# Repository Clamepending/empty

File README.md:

# PCB-Repair

PCB-Repair is a reinforcement-learning environment and evaluation in which an agent repairs small
printed-circuit-board designs. Each design has a schematic of record (`design.json`) and a KiCad 7
layout (`board.kicad_pcb`). Each normal-tier task contains 1–3 injected faults: wrong component
values, broken or swapped connections, wrong footprints, undersized power tracks, misplaced
decoupling capacitors, and so on. Hard-tier tasks (mostly 20–27-part multi-rail boards) contain
3–6 faults, at least two of them *latent*: invisible to every `pcbtool` check but deducible from the
datasheets, the design intent and the stated design rules. The agent works with ordinary shell commands plus a domain CLI (`pcbtool`). A
deterministic verifier then grades the two deliverable files against a hidden golden reference.
The verifier applies structural gates and also runs KiCad DRC, an ERC, SPICE spec assertions
(ngspice) and layout checks. The reward is binary: it is 1 only if every gate and check passes.
Because the reward is checked rather than judged by a model, it equals correctness. Every task is
procedurally generated, so the generator can produce fresh, uncontaminated tasks on demand.

## Quickstart (Ubuntu 24.04, about 10 min)

Run every command from the repo root, in order. Each one was timed on a 4-core host (see
`docs/ONBOARDING.md` for the measured times). Nothing here needs network access or Docker.

### 0. Preflight

```bash
python3 -c "import pcbnew, numpy, yaml; print('ok', pcbnew.Version())" && ngspice --version | grep -m1 ngspice
```

This must print `ok 7.0.11` and an `ngspice-42` line. If it does not:

- **KiCad 7.0.11 and ngspice** come from apt: `sudo apt-get install -y kicad=7.0.11* kicad-footprints=7.0.11* ngspice`.
  The `pcbnew` module lands in `/usr/lib/python3/dist-packages`. It works with whichever `python3` the
  apt KiCad build supports. On the reference host that is Python 3.13. `pcbnew` is not on PyPI.
- **numpy, pyyaml and pytest** come from pip for that same `python3`:
  `python3 -m pip install numpy pyyaml pytest`.
  On a stock Ubuntu 24.04 python (3.12, "externally managed") you need either `--break-system-packages`
  or the apt packages `python3-numpy python3-yaml python3-pytest`.
  The apt packages are built for the distro python only. If your `python3` is a different version
  (as on the reference host, 3.13), they are invisible to it and you must use pip.
- Alternatively, use a venv that can see `pcbnew`:
  `python3 -m venv --system-site-packages .venv && . .venv/bin/activate && pip install -e .`
  This was tested: it also puts `pcbtool` on PATH and makes `import pcbenv` work from any directory.

### 1. Get tasks

The bundles in `dist/` are extracted into `data/v2/<split>/<task_id>/`. That is the same layout as
`tasks/v2/` in a git checkout, so split names such as `v2/normal` work on both. Extract into a
separate directory (`data/`), not into the checkout's `tasks/`.

```bash
export PATH="$PWD/bin:$PATH"                                            # puts pcbtool on PATH
python3 -m pcbenv.api extract dist/pcb-repair-v2.1-normal.tar.gz data       # 655 tasks -> data/v2/normal/
python3 -m pcbenv.api extract dist/pcb-repair-v2.1-hard.tar.gz data         # 370 tasks -> data/v2/hard/
python3 -m pcbenv.api splits data                                         # v2/hard 370, v2/normal 655
```

Other bundles:

- `pcb-repair-v2.1-hard-layout.tar.gz` gives `v2/hard_layout`.
- `-normal-holdout`, `-hard-holdout` and `-hard-layout-holdout` give the `*_holdout` splits. Keep these out of training.

In a git checkout, `tasks/` already holds every split, so `tasks` can replace `data` in every
command below.

A `--split` that matches nothing prints the splits that do exist and exits 2. Bundle names
(`pcb-repair-v2.1-normal`) and bare names (`normal`) are accepted as aliases.

### 2. List tasks (normal and hard tier)

```bash
python3 -m pcbenv.api list data --split v2/normal | head -3               # split  task_id  family  path
python3 -m pcbenv.api list data --split v2/hard   | head -3               # the hard tier
```

### 3. Scripted demo policy: one task, then 20 tasks

```bash
python3 examples/demo_policy.py --make-demo runs/pcb_demo --transcript runs/demo.jsonl          # reward 1, ~2 s
python3 examples/demo_policy.py --tasks data --split v2/normal --split v2/hard --limit 10 \
    --workers 4 --max-seconds 20 --transcript runs/demo20.jsonl                                  # 10 normal + 10 hard, ~30 s
```

The demo policy only solves **single wrong-value faults**, so its mean reward on real tasks is low
(1/20 = 0.05 on the 20 tasks above). It reads `design.json` and `spec.json`, runs at most 20 local
simulations, then calls `set-value`, `check` and `submit`. It is a plumbing demo, not a baseline.

Its limits:

- `--max-seconds` (default 20) caps each episode's acting time. Grading adds about 1–5 s on top.
- `--max-sims` (default 20) caps its simulations.

Each line it prints is one episode.

`runs/demo20.jsonl` is the transcript, with `start`, `step` and `result` rows. Every `start` row
has a matching `result` row. If an episode is interrupted (Ctrl-C, SIGTERM), its `result` row has
`"aborted": true` and reward 0. If it hits `--max-seconds`, the row has `"timed_out": true` and the
files are graded as they are.

### 4. Work one task by hand

```bash
T=$(python3 -m pcbenv.api list data --split v2/normal --json | head -1 | python3 -c 'import json,sys; print(json.load(sys.stdin)["path"])')
rm -rf runs/work && mkdir -p runs/work && cp -r "$T/public/." runs/work/   # PUBLIC files only; safe to rerun
(cd runs/work && pcbtool check)                                            # exit 1: this task is faulty
python3 -m pcbenv.api verify runs/work "$T"                                # gates/checks JSON; exit 1 here (reward 0 until fixed)
```

`pcbtool --help` lists the inspect and edit commands (`show`, `sim`, `drc`, `set-value`, `connect`,
`route`, ...). TASK.md in the workdir is the problem statement.

### 5. Batch: JSONL export and scoring predictions

```bash
python3 -m pcbenv.adapters.jsonl export --tasks data --split v2/normal --out runs/train.jsonl     # 655 rows, public files only
python3 -m pcbenv.adapters.jsonl predict-unchanged --tasks data --split v2/normal --limit 5 --out runs/preds.jsonl
python3 -m pcbenv.adapters.jsonl score --tasks data --predictions runs/preds.jsonl --out runs/scores.jsonl --workers 4
```

A predictions file has one JSON object per line. Each line holds the task id and the full text of
the two deliverables, and any other key is ignored:

```json
{"id": "pcbr2-normal-0076521e", "design.json": "{\"components\": {...}, ...}", "board.kicad_pcb": "(kicad_pcb (version 20221018) ..."}
```

`predict-unchanged` writes exactly this format with the unmodified public files. It is a template,
and it scores 0 on every task. `score` prints `{"n", "mean_reward"}`. Its `--out` file has one row
per prediction, in input order: `{"id", "reward", "gates", "checks", "failed", "error"}`.

Rows in the export's `{"files": {"design.json": {"encoding", "content"}}}` form are accepted too.
Load the export with `datasets.load_dataset("json", data_files="runs/train.jsonl")`.

### 6. Tests

```bash
python3 -m pytest -q tests/test_v2_hardening.py tests/test_harness.py tests/test_adapters.py tests/test_onboarding_paths.py   # ~1 min
python3 -m pytest -q tests/                                                                     # full suite, ~15 min
```

## Plug in your own policy or model

`run_agent(task_dir, call_model, ...)` runs one episode, grades it, and appends a transcript. You
supply `call_model(messages, tools) -> reply`.

- **`messages`** is a provider-neutral list:
  - `{"role": "system"|"user", "content": str}`
  - `{"role": "assistant", "content", "tool_calls", "raw"}`
  - `{"role": "tool", "tool_call_id", "name", "content"}`
- **`tools`** are the three tool definitions: `bash {cmd}`, `pcbtool {args: [...]}` and `submit {}`.
- **The reply** is `{"tool_calls": [{"name", "input"}, ...], "text": ...}`, or a single
  `{"name", "input"}`. `None` (no tool calls) submits.

Save this as `my_policy.py` in the repo root and run `python3 my_policy.py` (saved anywhere else, run it as `PYTHONPATH=/path/to/repo python3 my_policy.py`, or use the editable install above):

```python
from pcbenv import api
from pcbenv.adapters.rollout import run_agent

def call_model(messages, tools):
    n = sum(m["role"] == "tool" for m in messages)     # tool results seen so far
    if n == 0:
        return {"tool_calls": [{"name": "pcbtool", "input": {"args": ["sim"]}}], "text": "check the spec"}
    if n == 1:
        return {"name": "bash", "input": {"cmd": "head -c 400 design.json"}}
    return None                                         # no tool call -> submit and grade

ref = api.list_tasks("data", split="v2/normal")[0]
row = run_agent(ref.path, call_model, max_steps=10, max_seconds=60, model="my-policy",
                transcript="runs/my_policy.jsonl")
print(ref.task_id, row["reward"], row["failed"])
```

`tool_style="anthropic"` or `"openai"` passes the tool definitions in that provider's schema
(`gym_like.anthropic_style_tools()` / `openai_style_tools()`). Exceptions raised by `call_model` end
the episode with `error` set, and the files are still graded.

**Anthropic models:** `pip install anthropic`, then run
`python3 examples/run_with_claude.py MODEL_ID --tasks data --split v2/normal --limit 5`.
This needs network access and an API key.

**Inspect (UK AISI)** is optional and not part of the timed path above. It needs network access
(`pip install inspect-ai`) and a running Docker daemon (the sandbox image is built with
`docker build --target agent -t pcb-repair-agent .`). The task reads `tasks/` by default, so pass
`-T tasks_root=data` for extracted bundles:

```bash
inspect eval pcbenv/adapters/inspect_task.py@pcb_repair -T tasks_root=data -T split=v2/normal -T limit=5 --model anthropic/<model-id>
```

Without `inspect_ai` installed, `pcb_repair()` raises an ImportError with this install hint.
`inspect_task.build_samples("data", split="v2/normal", limit=3)` works without it.

## Python API

Run Python from the repo root, or set `export PYTHONPATH=/path/to/repo`, or use the `pip install -e .`
venv from the preflight section.

```python
from pcbenv import api
tasks = api.list_tasks("data", split="v2/normal")          # [TaskRef(task_id, path, split, family, difficulty)]
hard = api.list_tasks("data", split="v2/hard")             # hard tier; api.available_splits("data") lists all
task = api.load_task(tasks[0].path)                         # TASK.md, spec, public file list (no hidden data)
with api.PcbRepairEnv(max_steps=40) as env:                 # gym-like: reset / step / reward
    obs = env.reset(task.path)                              # {"task_md", "files", "workdir"}
    obs, reward, terminated, truncated, info = env.step({"tool": "pcbtool", "args": ["check"]})
    obs, reward, terminated, truncated, info = env.step({"tool": "submit"})   # reward is 0.0 or 1.0
res = api.verify(task.public_dir, task.path)                # VerifyResult; isolated subprocess; never raises
print(res.reward, res.gates, res.checks)                    # dataclass: res.to_json() / dataclasses.asdict(res)
```

| Module | What it is for |
|---|---|
| `pcbenv.api` | stable surface: `list_tasks`, `available_splits`, `load_task`, `verify`, `extract_tasks`, `PcbRepairEnv` |
| `pcbenv.adapters.gym_like` | action JSON schema, `openai_style_tools()`, `anthropic_style_tools()`, `tool_call_to_action()` |
| `pcbenv.adapters.rollout` | `run_agent(task_dir, call_model, max_steps, max_seconds=...)`, which writes a JSONL transcript (the calibration log format) |
| `pcbenv.adapters.jsonl` | `export_jsonl` (HF-datasets style rows) and `score_jsonl(predictions)` (batch, parallel, isolated) |
| `pcbenv.adapters.inspect_task` | UK AISI Inspect `Task`: sandboxed `bash` + `pcbtool`, with a host-side verifier scorer |

A task directory looks like this (`tasks/` in a checkout, `data/` after `extract`):

```
<root>/v2/<split>/<task_id>/
  public/  TASK.md  design.json  board.kicad_pcb  spec.json  parts/<PART>.md  [tools.json]  <- the agent sees only this
  hidden/  golden_design.json  golden_board.kicad_pcb  meta.json                <- the grader reads only this
```

`tasks/manifest.jsonl` (checkout) or `data/v2/<split>/manifest.jsonl` (extracted) lists the tasks.
The splits are `v2/normal`, `v2/normal_holdout`, `v2/hard`, `v2/hard_holdout`, and the layout-rules
sub-tier `v2/hard_layout` and `v2/hard_layout_holdout`. Task ids are opaque
(`pcbr2-<tier>-<hash>`); see [reports/v2_generation.md](reports/v2_generation.md).

## How reward works

The verifier is `pcbenv/verify.py`. It reads only `design.json` and `board.kicad_pcb` from the
workdir. Each must be a regular file of at most 5 MB, and symlinks are refused. All reference data
comes from `hidden/`.

| Stage | Name | Passes when |
|---|---|---|
| gate | `parse` | both files load; design.json validates against the schema and the parts library |
| gate | `components` | same refs and parts as the golden; each footprint is in the part's allowed list, matches the board, and has library-identical pads |
| gate | `topology` | connectivity partition == golden (net names ignored; symmetric 2-pin parts may be flipped) |
| gate | `consistency` | board connectivity and values == design.json |
| gate | `integrity` | outline unchanged; no DRC exclusions or markers, added zones, copper graphics or inner-layer tracks |
| check | `drc` | KiCad DRC under the canonical rules: 0 errors, 0 unconnected |
| check | `erc` | no ERC errors (unconnected required pins, driver conflicts, missing supply, shorts, ...) |
| check | `spec` | every golden SPICE / analytic assertion passes on the candidate design |
| check | `values` | every component value inside its published range (`value_bounds`) |
| check | `layout` | power-net track widths ≥ required; each decoupling cap within its straight-line distance and copper-path length of its IC pin |
| check | `rules` | only for tasks with a rule context (all v2 tasks: resistor power; hard tier: all datasheet design rules) — not run by `pcbtool` |
| check | `layout_rules` | only for `hard_layout` tasks: board-geometry rules stated in TASK.md "Layout rules" / `spec.json:layout_rules` (Kelvin sense, switching-loop area, crystal traces, analog/switching separation) — not run by `pcbtool` |

**Reward = 1.0 if and only if all 5 gates and all checks (5, plus `rules` / `layout_rules` where present) pass, otherwise 0.0.** The per-gate and
per-check booleans are returned for diagnostics only. [docs/REWARD.md](docs/REWARD.md) covers what
each stage catches and its known limitations.

## Security boundary

`PcbRepairEnv` runs `bash` commands on the host as your user. **This is not a sandbox**: an agent
could read `hidden/` from there. That is fine for scripted policies and local development. For
evaluating or training untrusted models, use the two-image setup instead. The `agent` image
(`docker build --target agent`) holds the public files and the `pcbtool` code only, with no family
generators and no network. The `grader` image runs `pcbenv.verify` outside the agent container on
copies of the two deliverables. `docker/run_episode.sh` and the Inspect adapter both implement this
split. See [docs/SECURITY.md](docs/SECURITY.md).

## Task families & fault types

From [reports/v2_generation.md](reports/v2_generation.md) (train / holdout):

| Tier | Families | Faults per task | # tasks |
|---|---|---|---|
| normal | 10 v1 families: `ldo_reg`, `led_driver`, `npn_switch`, `nmos_switch`, `opamp_noninv`, `opamp_inv`, `rc_lowpass`, `divider_adc`, `mcu_i2c`, `xtal_osc` | 1–3 of 19 types (wrong values, swapped / floating pins, reversed polarity, decap misconnected or moved, broken / narrow / shorted traces, clearance, footprint and board-pad swaps, BOM mismatch) | 655 / 164 |
| hard | 4 composite boards (`sys_sensor_node`, `sys_motor_ctrl`, `sys_clocked_mcu`, `sys_analog_frontend`, 82 %) + 5 v1 families | 3–6, ≥ 2 latent (12 types: underrated parts, weak base drive, misplaced flyback, connector / MCU pin swaps, decap on the wrong rail, bias or pull-up to the wrong rail, bypassed protection diode), interacting value faults, 39 % no_autoroute | 370 / 92 |

## Limitations

- **Generic parts.** Parts such as `LDO_ADJ`, `OPAMP`, `MCU8` and `NPN` are synthetic generics with
  self-contained datasheets, not manufacturer part numbers.
- **SPICE models are behavioural approximations.** They are good enough to tell a correct design
  from a faulted one, but they are not sign-off models.
- **KiCad 7 only.** The `.kicad_pcb` files are KiCad 7.0.11 format; ports to KiCad 8/9 are not done.
- **Small boards.** Boards are 2-layer, about 6–16 components (hard-tier composites 20–27), using SMD/THT library footprints. The
  in-house maze router is simple: it is enough to make goldens DRC-clean, but it is not a
  production router.
- **Not checked:** signal or power integrity, EMI, thermal behaviour, manufacturability (beyond
  DRC), BOM cost or part availability.
- **One task kind: repair.** A golden plus injected faults (1–3 normal, 3–6 hard), with reference designators
  fixed. Open-ended design from a spec is planned for v2.
- **Binary reward.** Partial progress is visible in `gates`/`checks`, but the reward does not
  credit it. A design that differs from the golden yet is equally correct (for example, a different
  but valid resistor pair) passes only if it keeps the golden's topology and meets the same
  assertions.

## More

[docs/ARCHITECTURE.md](docs/ARCHITECTURE.md) (module map) · [docs/REWARD.md](docs/REWARD.md) ·
[docs/SECURITY.md](docs/SECURITY.md) · [docs/DATA_CARD.md](docs/DATA_CARD.md) ·
[docs/VERSIONING.md](docs/VERSIONING.md) · [docs/ONBOARDING.md](docs/ONBOARDING.md) (README dry run + timings) · Licence: **LICENSE-TBD (founder decision)**.

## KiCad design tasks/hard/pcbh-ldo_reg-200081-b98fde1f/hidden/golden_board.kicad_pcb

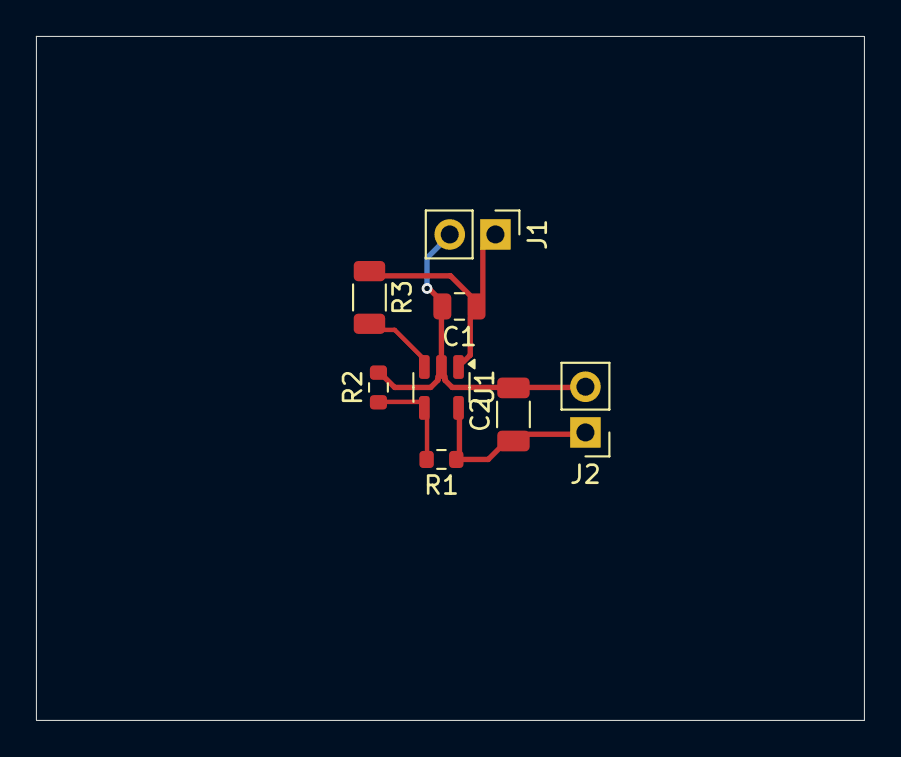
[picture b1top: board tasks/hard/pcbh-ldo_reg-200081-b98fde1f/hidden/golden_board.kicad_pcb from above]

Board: 2 copper layers, 46.0 x 38.0 mm, 8 parts (0 on the bottom side), 5 nets.

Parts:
C1: 4.7u; C_0805_2012Metric
C2: 4.7u; C_1206_3216Metric
J1, J2: PinHeader_1x02_P2.54mm_Vertical
R1: 86.6k; R_0603_1608Metric
R2: 28k; R_0603_1608Metric
R3: 220k; R_1206_3216Metric
U1: SOT-23-5

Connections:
+3V3: C2.1, J2.1, R1.1, U1.5
EN: R3.2, U1.3
FB: R1.2, R2.1, U1.4
GND: C1.2, C2.2, J1.2, J2.2, R2.2, U1.2
VIN: C1.1, J1.1, R3.1, U1.1

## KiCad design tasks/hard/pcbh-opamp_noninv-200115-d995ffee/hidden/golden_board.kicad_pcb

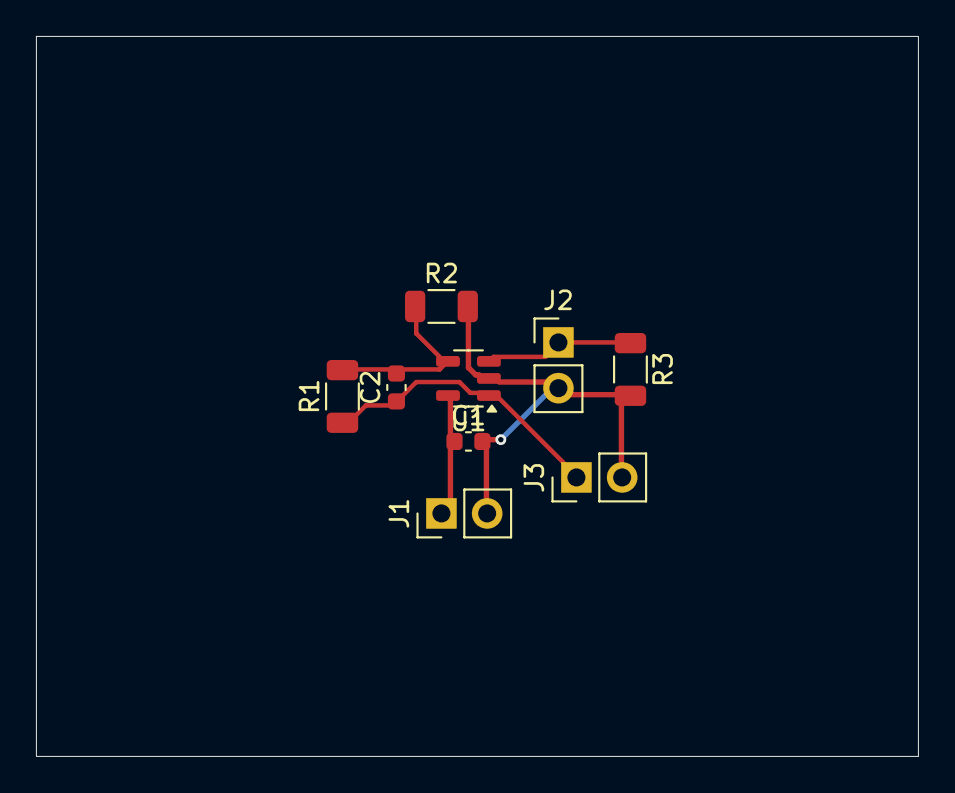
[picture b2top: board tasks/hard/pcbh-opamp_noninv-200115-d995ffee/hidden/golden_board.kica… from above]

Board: 2 copper layers, 49.0 x 40.0 mm, 9 parts (0 on the bottom side), 5 nets.

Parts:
C1: 100n; C_0603_1608Metric
C2: 150p; C_0603_1608Metric
J1, J2, J3: PinHeader_1x02_P2.54mm_Vertical
R1: 14.7k; R_1206_3216Metric
R2: 7.32k; R_1206_3216Metric
R3: 220k; R_1206_3216Metric
U1: SOT-23-5

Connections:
FB: C2.2, R1.2, R2.1, U1.4
GND: C1.2, J1.2, J2.2, J3.2, R2.2, R3.2, U1.2
IN: J2.1, R3.1, U1.3
OUT: C2.1, J3.1, R1.1, U1.1
VCC: C1.1, J1.1, U1.5

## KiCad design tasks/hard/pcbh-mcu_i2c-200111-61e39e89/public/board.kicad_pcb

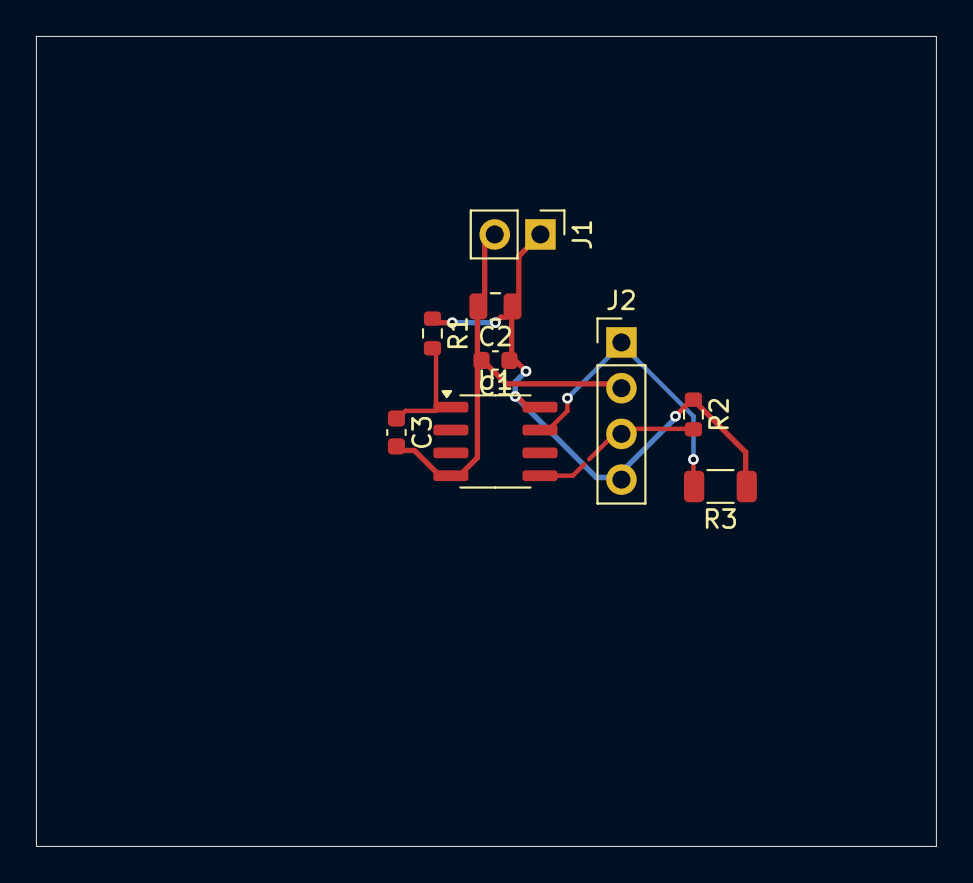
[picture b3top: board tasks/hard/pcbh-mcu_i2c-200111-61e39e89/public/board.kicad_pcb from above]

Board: 2 copper layers, 50.0 x 45.0 mm, 9 parts (0 on the bottom side), 5 nets.

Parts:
C1: 100n; C_0603_1608Metric
C2: 1u; C_0805_2012Metric
C3: 100p; C_0603_1608Metric
J1: PinHeader_1x02_P2.54mm_Vertical
J2: PinHeader_1x04_P2.54mm_Vertical
R1: 7.5k; R_0603_1608Metric
R2: 16k; R_0603_1608Metric
R3: 16k; R_1206_3216Metric
U1: SOIC-8_3.9x4.9mm_P1.27mm

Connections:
+2V5: C1.1, C2.1, J1.1, J2.4, R1.1, R2.1, R3.1, U1.8
GND: C1.2, C2.2, C3.2, J1.2, J2.2, U1.4
NRST: C3.1, R1.2, U1.1
SCL: J2.1, R3.2, U1.7
SDA: J2.3, R2.2, U1.5

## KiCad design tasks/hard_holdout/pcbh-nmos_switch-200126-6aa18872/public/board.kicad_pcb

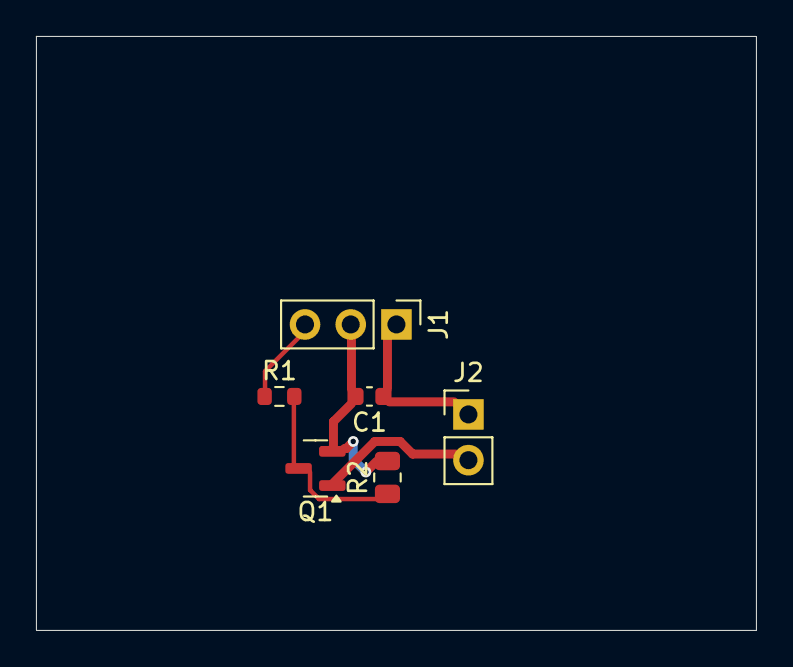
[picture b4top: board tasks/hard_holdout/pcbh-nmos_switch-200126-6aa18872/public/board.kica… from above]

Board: 2 copper layers, 40.0 x 33.0 mm, 6 parts (0 on the bottom side), 5 nets.

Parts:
C1: 2.2u; C_0603_1608Metric
J1: PinHeader_1x03_P2.54mm_Vertical
J2: PinHeader_1x02_P2.54mm_Vertical
Q1: SOT-23
R1: 27; R_0603_1608Metric
R2: 30k; R_0805_2012Metric

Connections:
+24V: C1.1, J1.1, J2.1
CTRL: J1.3, R1.1
GATE: Q1.3, R1.2, R2.1
GND: C1.2, J1.2, Q1.2, R2.2
SW: J2.2, Q1.1

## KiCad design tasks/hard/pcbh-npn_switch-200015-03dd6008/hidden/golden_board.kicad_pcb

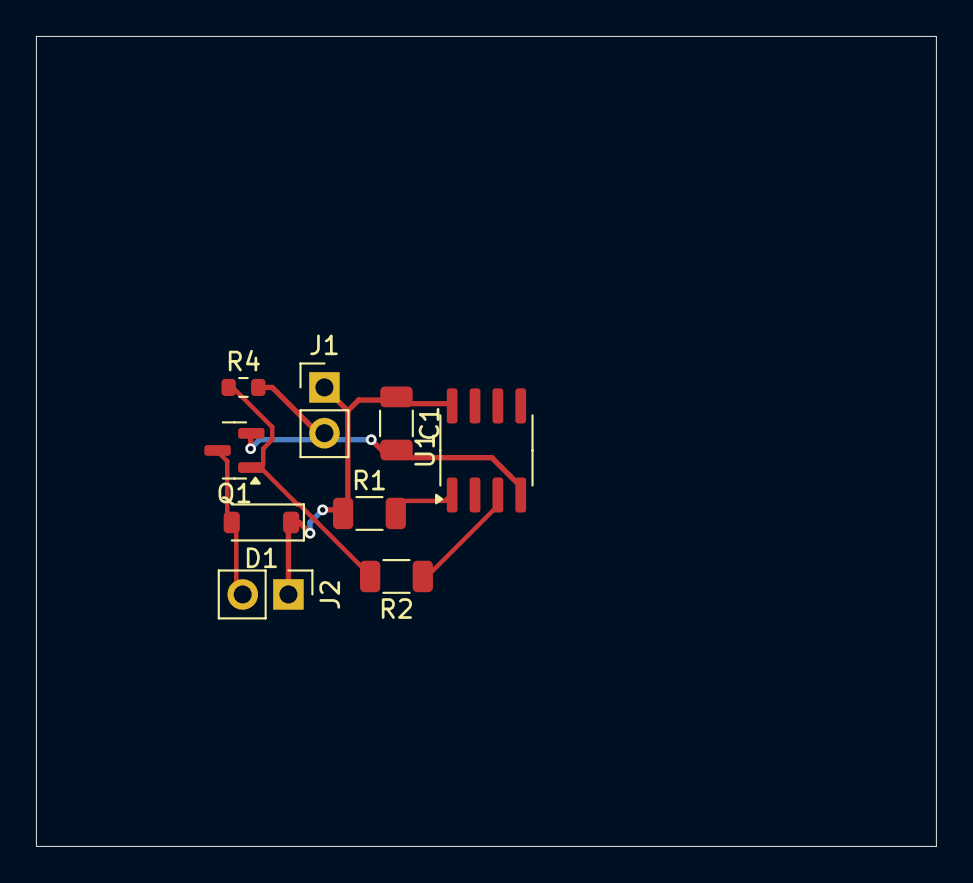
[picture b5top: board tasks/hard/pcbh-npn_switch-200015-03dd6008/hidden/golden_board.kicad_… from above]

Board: 2 copper layers, 50.0 x 45.0 mm, 9 parts (0 on the bottom side), 6 nets.

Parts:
C1: 100n; C_1206_3216Metric
D1: D_SOD-123
J1, J2: PinHeader_1x02_P2.54mm_Vertical
Q1: SOT-23
R1: 27k; R_1206_3216Metric
R2: 1.2k; R_1206_3216Metric
R4: 30k; R_0603_1608Metric
U1: SOIC-8_3.9x4.9mm_P1.27mm

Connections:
+5V: C1.1, D1.1, J1.1, J2.1, R1.1, U1.8
BASE: Q1.1, R2.2, R4.1
CTRL: R2.1, U1.3
GND: C1.2, J1.2, Q1.2, R4.2, U1.4
NRST: R1.2, U1.1
SW: D1.2, J2.2, Q1.3

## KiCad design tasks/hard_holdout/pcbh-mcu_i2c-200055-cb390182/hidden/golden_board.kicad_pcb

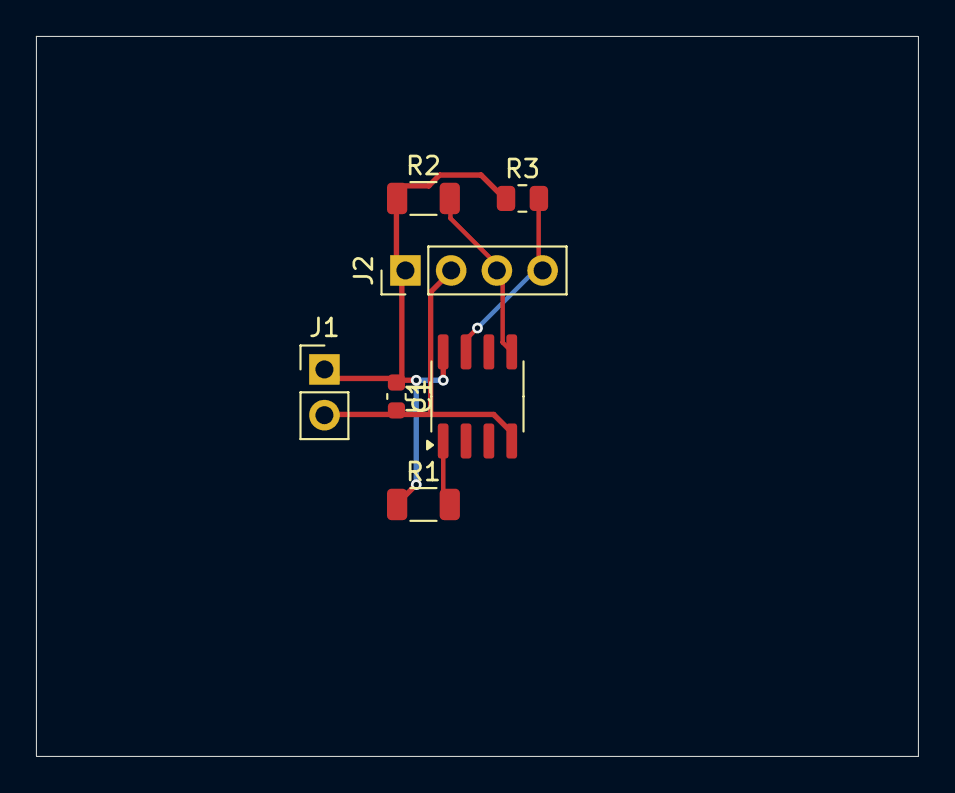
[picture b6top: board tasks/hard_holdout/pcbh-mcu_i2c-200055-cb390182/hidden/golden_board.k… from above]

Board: 2 copper layers, 49.0 x 40.0 mm, 7 parts (0 on the bottom side), 5 nets.

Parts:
C1: 100n; C_0603_1608Metric
J1: PinHeader_1x02_P2.54mm_Vertical
J2: PinHeader_1x04_P2.54mm_Vertical
R1: 27k; R_1206_3216Metric
R2: 1.1k; R_1206_3216Metric
R3: 1.1k; R_0805_2012Metric
U1: SOIC-8_3.9x4.9mm_P1.27mm

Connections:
+2V5: C1.1, J1.1, J2.1, R1.1, R2.1, R3.1, U1.8
GND: C1.2, J1.2, J2.2, U1.4
NRST: R1.2, U1.1
SCL: J2.4, R3.2, U1.7
SDA: J2.3, R2.2, U1.5

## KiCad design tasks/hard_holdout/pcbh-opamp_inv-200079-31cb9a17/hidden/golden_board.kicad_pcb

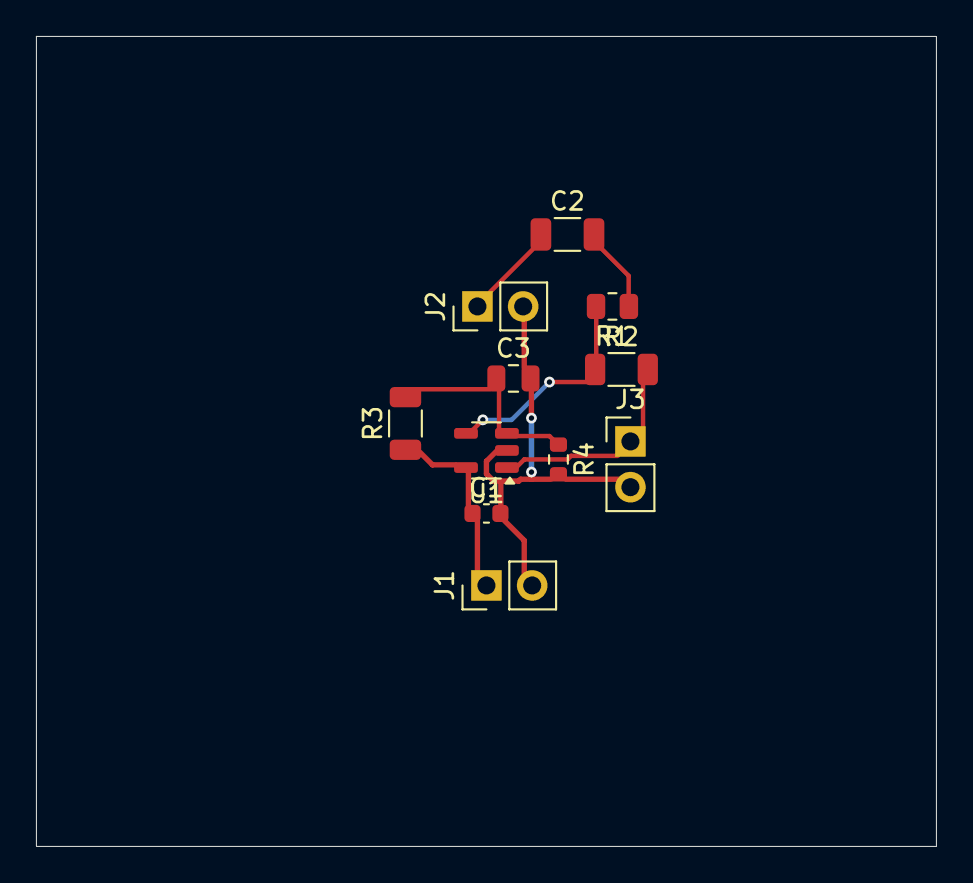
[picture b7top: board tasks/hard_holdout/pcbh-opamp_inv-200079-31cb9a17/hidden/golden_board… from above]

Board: 2 copper layers, 50.0 x 45.0 mm, 11 parts (0 on the bottom side), 7 nets.

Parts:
C1: 100n; C_0603_1608Metric
C2: 680n; C_1206_3216Metric
C3: 4.7u; C_0805_2012Metric
J1, J2, J3: PinHeader_1x02_P2.54mm_Vertical
R1: 11.8k; R_0805_2012Metric
R2: 118k; R_1206_3216Metric
R3: 82k; R_1206_3216Metric
R4: 82k; R_0603_1608Metric
U1: SOT-23-5

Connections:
GND: C1.2, C3.2, J1.2, J2.2, J3.2, R4.2, U1.2
IN: C2.1, J2.1
IN_AC: C2.2, R1.1
OUT: J3.1, R2.2, U1.1
SUM: R1.2, R2.1, U1.4
VCC: C1.1, J1.1, R3.1, U1.5
VMID: C3.1, R3.2, R4.1, U1.3

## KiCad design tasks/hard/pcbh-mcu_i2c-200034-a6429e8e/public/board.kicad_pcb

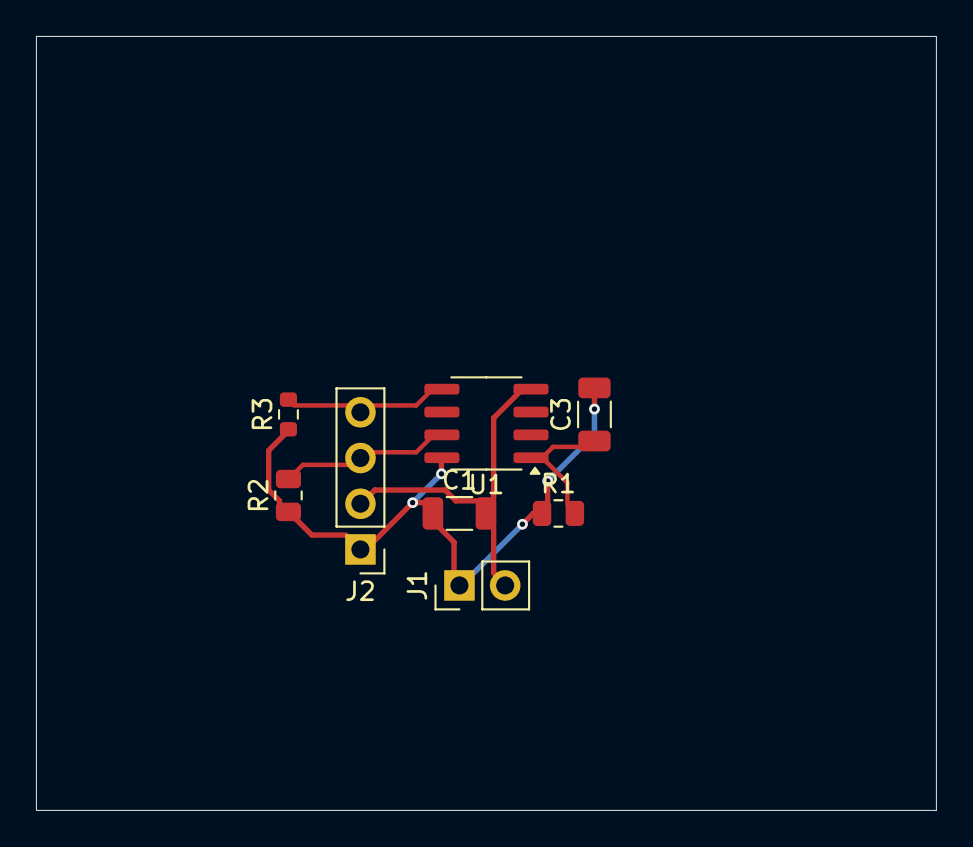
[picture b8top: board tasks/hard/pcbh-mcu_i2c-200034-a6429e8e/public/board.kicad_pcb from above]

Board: 2 copper layers, 50.0 x 43.0 mm, 8 parts (0 on the bottom side), 5 nets.

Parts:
C1, C3: 100n; C_1206_3216Metric
J1: PinHeader_1x02_P2.54mm_Vertical
J2: PinHeader_1x04_P2.54mm_Vertical
R1: 39k; R_0805_2012Metric
R2: 100k; R_0805_2012Metric
R3: 4.3k; R_0603_1608Metric
U1: SOIC-8_3.9x4.9mm_P1.27mm

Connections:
+5V: C1.1, C3.2, J1.1, J2.1, R1.1, R2.1, R3.1, U1.8
GND: C1.2, J1.2, J2.2, U1.4
NRST: C3.1, R1.2, U1.1
SCL: J2.4, R3.2, U1.5
SDA: J2.3, R2.2, U1.7
